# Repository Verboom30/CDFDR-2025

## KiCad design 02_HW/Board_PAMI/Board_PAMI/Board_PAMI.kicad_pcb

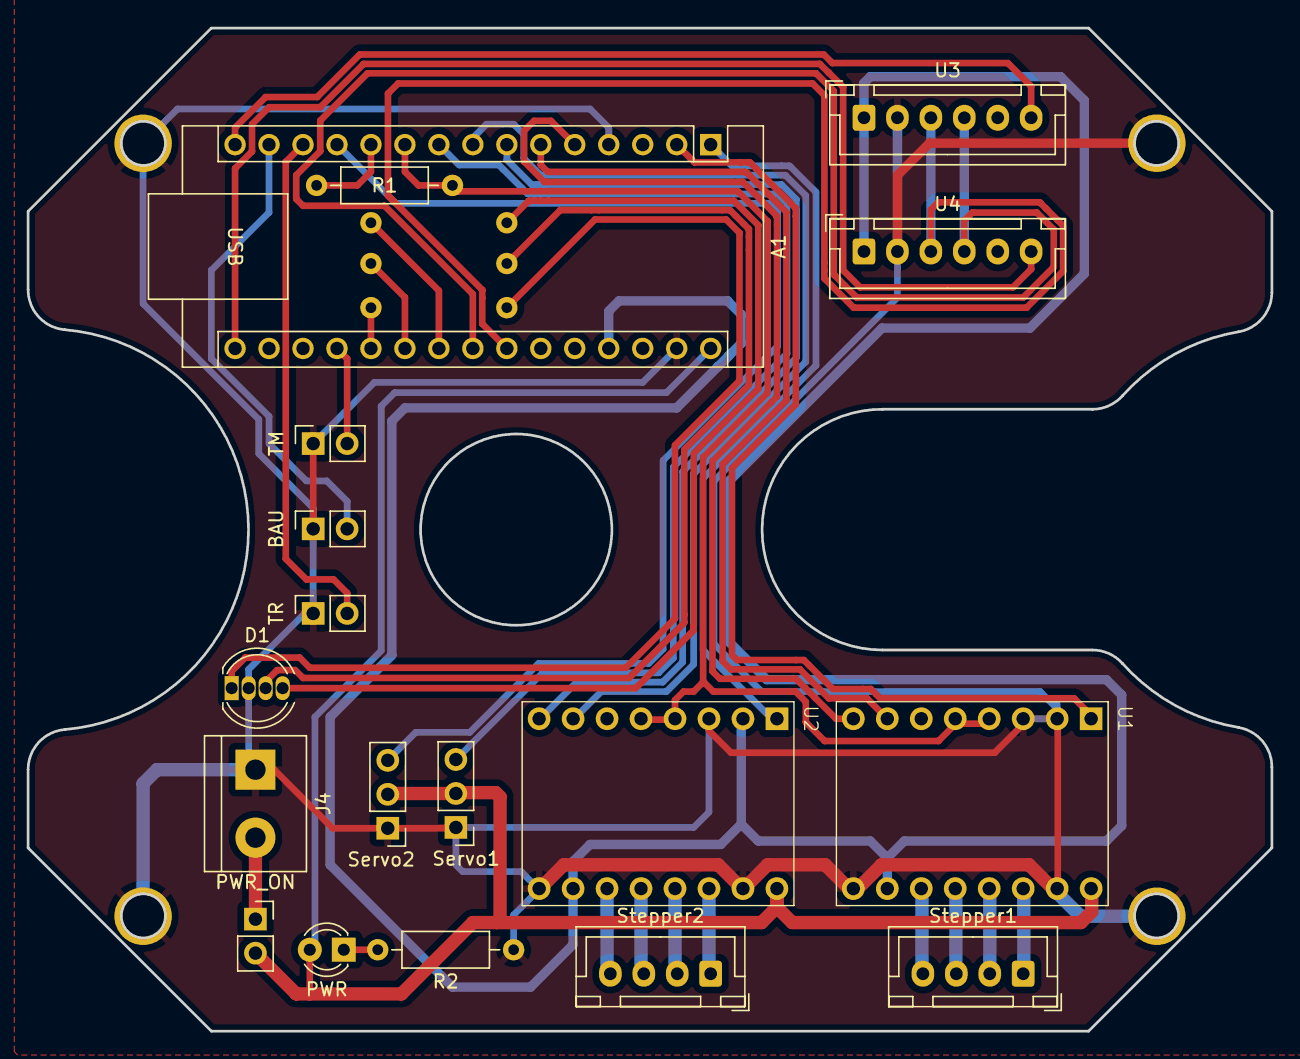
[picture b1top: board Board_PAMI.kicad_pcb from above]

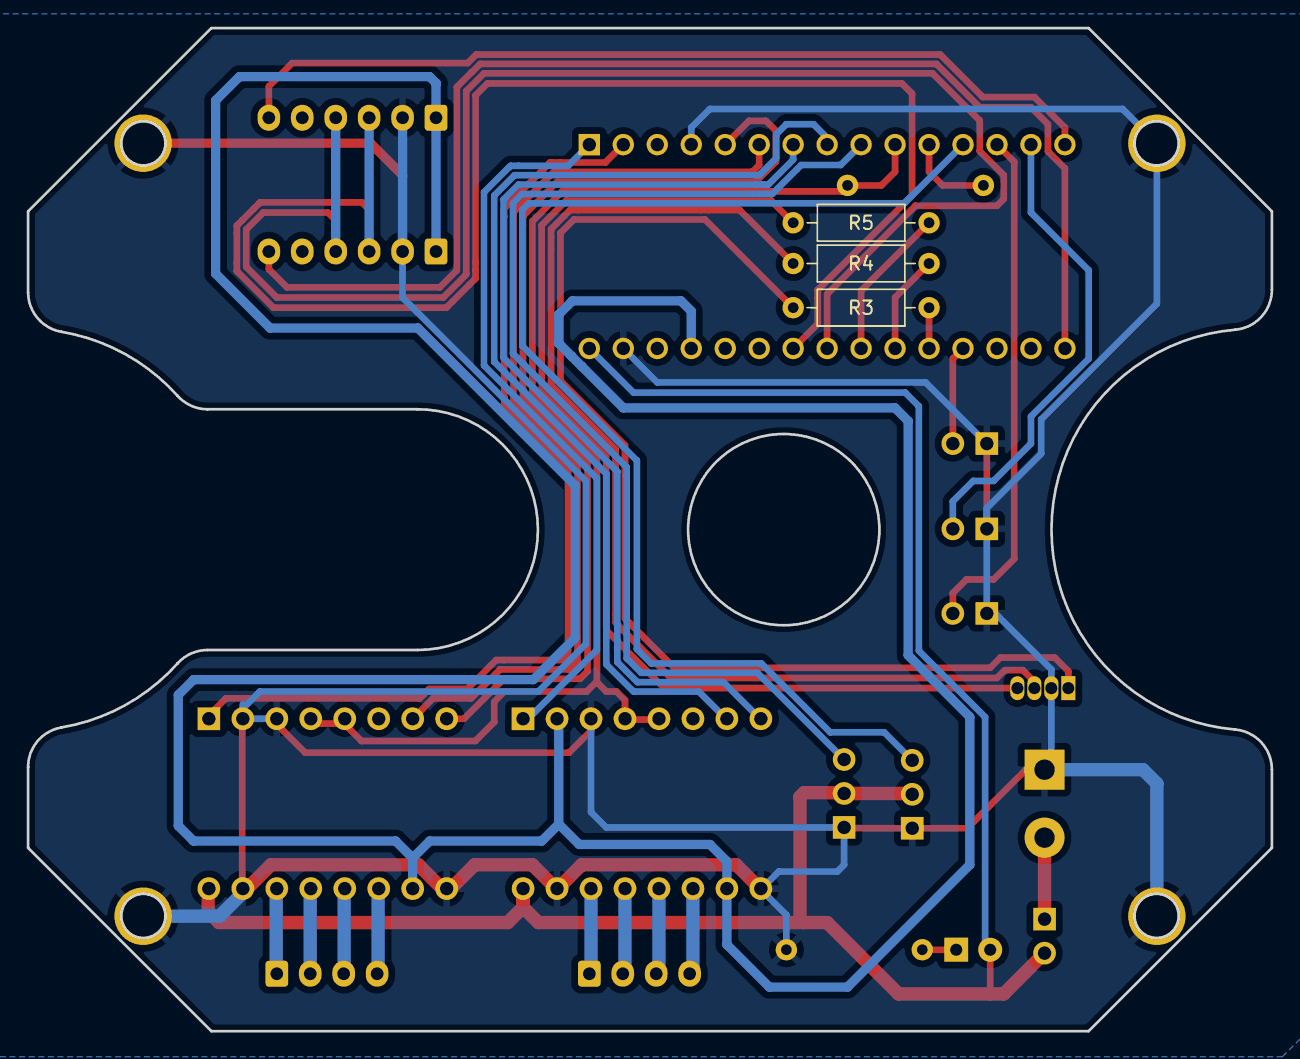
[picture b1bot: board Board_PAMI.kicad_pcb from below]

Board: 2 copper layers, 93.0 x 75.0 mm, 25 parts (3 on the bottom side), 36 nets.

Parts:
A1: Arduino_Nano_v3.x; Arduino_Nano
BAU: SW_BAU; PinSocket_1x02_P2.54mm_Vertical
D1: LED_BGKR; LED_D5.0mm-4_RGB_HOME
H1, H2, H3, H4: MountingHole_Pad; MountingHole_3.2mm_M3_DIN965_Pad_home
J4: ALIM; TerminalBlock_bornier-2_P5.08mm
PWR: LED_PWR; LED_D3.0mm
PWR_ON: PW_ON; PinSocket_1x02_P2.54mm_Vertical
R1: 1K; R_Axial_DIN0207_L6.3mm_D2.5mm_P10.16mm_Horizontal
R2, R3, R4, R5: 220R; R_Axial_DIN0207_L6.3mm_D2.5mm_P10.16mm_Horizontal
Servo1: SERVO_1; PinHeader_1x03_P2.54mm_Vertical
Servo2: SERVO_2; PinHeader_1x03_P2.54mm_Vertical
Stepper1: STEPPER_1; JST_XH_B4B-XH-A_1x04_P2.50mm_Vertical
Stepper2: STEPPER_2; JST_XH_B4B-XH-A_1x04_P2.50mm_Vertical
TM: SW_TEAM; PinSocket_1x02_P2.54mm_Vertical
TR: SW_TIRETTE; PinSocket_1x02_P2.54mm_Vertical
U1, U2: TMC2209
U3, U4: VL53L0XV2; JST_XH_B6B-XH-A_1x06_P2.50mm_Vertical

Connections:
/6V: J4.2, PWR_ON.1 (A)
DIR_1: A1.5 (D2), U1.8 (DIR)
DIR_2: A1.7 (D4), U2.8 (DIR)
EN_STP_1: A1.2 (D0/RX), U1.1 (EN)
EN_STP_2: A1.1 (D1/TX), U2.1 (EN)
GND: A1.4 (GND), A1.29 (GND), BAU.1, D1.3 (K), H1.1, H2.1, H3.1, H4.1, J4.1, R2.1, Servo1.1, Servo2.1, TM.1 (A), TR.1 (A), U1.2 (MS1), U1.3 (MS2), U1.10 (GND), U1.16 (GND), U2.3 (MS2), U2.10 (GND), U2.16 (GND), U3.2 (GND), U4.2 (GND)
LED_B: A1.22 (A3), R5.2
LED_G: A1.21 (A2), R4.2
LED_R: A1.20 (A1), R3.2
unnamed: A1.11 (D8), R1.2
unnamed: D1.1 (BA), R5.1
unnamed: D1.2 (GA), R4.1
unnamed: D1.4 (RA), R3.1
unnamed: PWR.1 (K), R2.2
unnamed: Stepper1.1, U1.11 (A2)
unnamed: Stepper1.2, U1.12 (A1)
unnamed: Stepper1.3, U1.13 (B1)
unnamed: Stepper1.4, U1.14 (B2)
unnamed: Stepper2.1, U2.11 (A2)
unnamed: Stepper2.2, U2.12 (A1)
unnamed: Stepper2.3, U2.13 (B1)
unnamed: Stepper2.4, U2.14 (B2)
PWM_SERVO_1: A1.9 (D6), Servo1.3
PWM_SERVO_2: A1.12 (D9), Servo2.3
SCL: A1.24 (A5), U3.3 (SCL), U4.3 (SCL)
SDA: A1.23 (A4), U3.4 (SDA), U4.4 (SDA)
STEP_1: A1.6 (D3), U1.7 (STEP)
STEP_2: A1.8 (D5), U2.7 (STEP)
SW_BAU: A1.14 (D11), BAU.2
SW_TM: A1.19 (A0), TM.2 (B)
SW_TR: A1.13 (D10), TR.2 (B)
UART_RX: A1.10 (D7), R1.1, U1.4 (UART_RX), U1.5 (UART_TX), U2.4 (UART_RX), U2.5 (UART_TX)
VCC: A1.27 (+5V), U1.15 (VCC), U2.2 (MS1), U2.15 (VCC), U3.1 (VCC), U4.1 (VCC)
VM: A1.30 (VIN), PWR.2 (A), PWR_ON.2 (B), Servo1.2, Servo2.2, U1.9 (VM), U2.9 (VM)
XSHUT_1: A1.15 (D12), U3.6 (XSHUT)
XSHUT_2: A1.16 (D13), U4.6 (XSHUT)

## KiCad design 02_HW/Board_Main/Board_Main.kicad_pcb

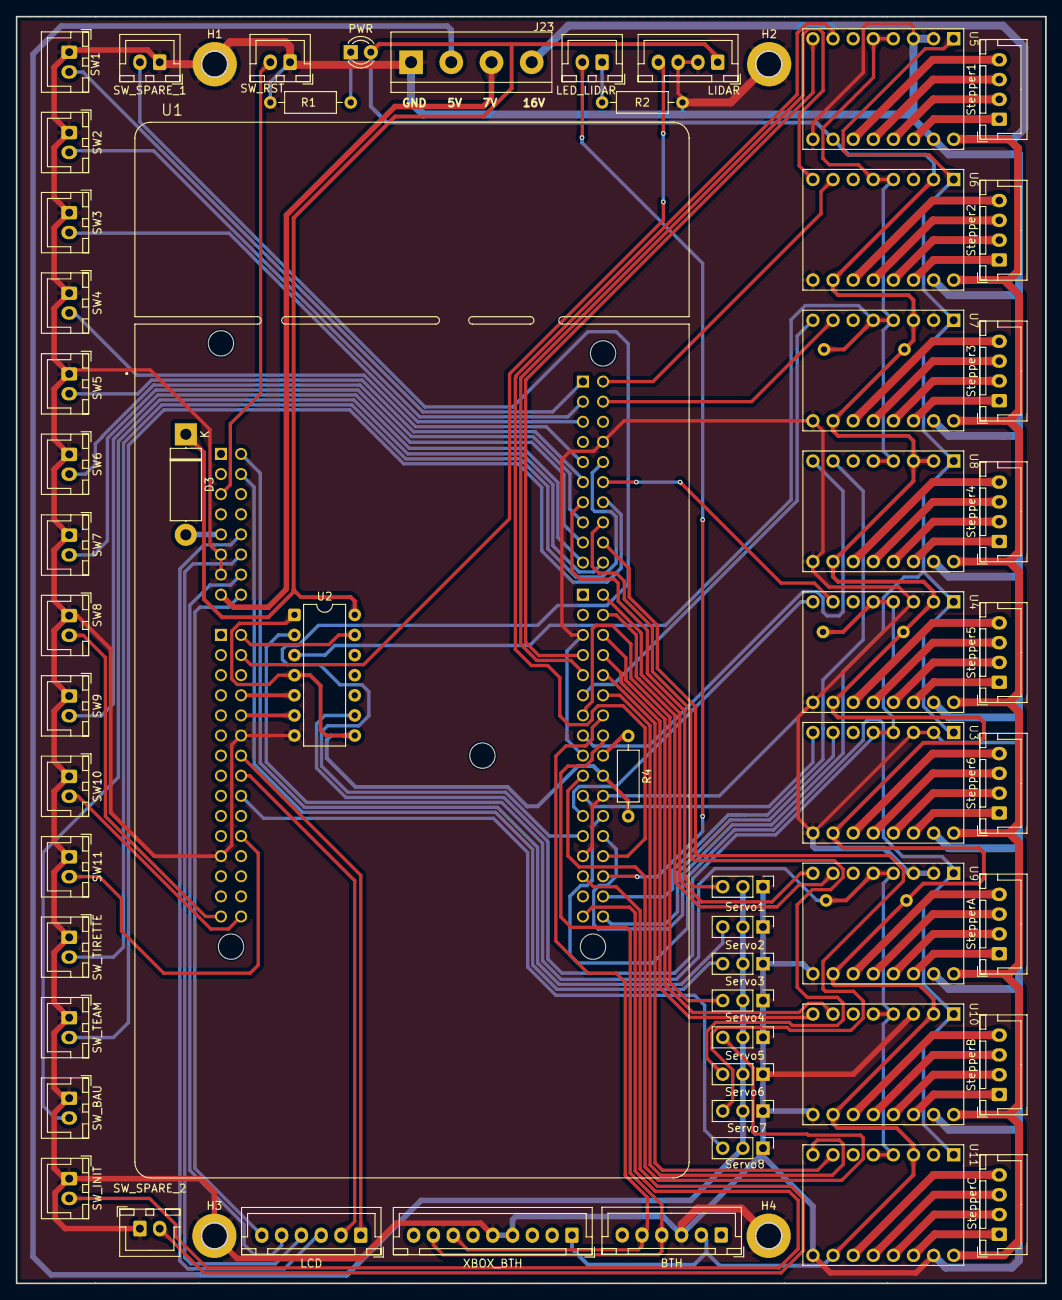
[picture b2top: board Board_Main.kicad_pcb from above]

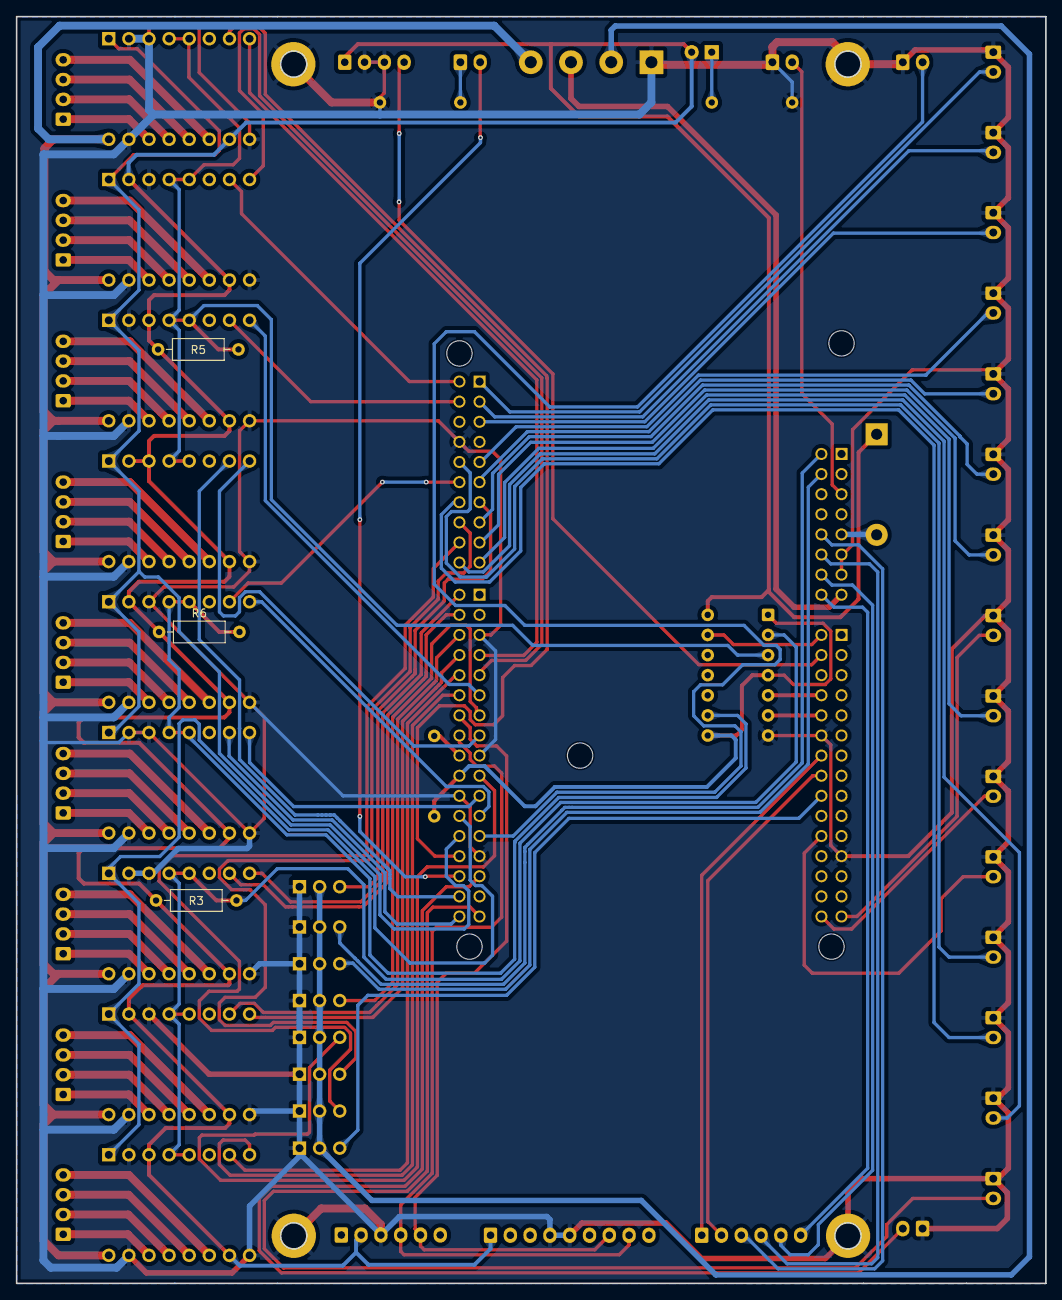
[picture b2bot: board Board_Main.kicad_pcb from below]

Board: 2 copper layers, 130.0 x 160.0 mm, 64 parts (3 on the bottom side), 108 nets.

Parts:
BTH: BTH; JST_XH_B6B-XH-A_1x06_P2.50mm_Vertical
D3: D; D_5W_P12.70mm_Horizontal
H1, H2, H3, H4: MountingHole_Pad; MountingHole_3.2mm_M3_DIN965_Pad
J23: ALIM; TerminalBlock_bornier-4_P5.08mm
LCD: LCD; JST_XH_B6B-XH-A_1x06_P2.50mm_Vertical
LED_LIDAR: LED_LIDAR; JST_XH_B2B-XH-A_1x02_P2.50mm_Vertical
LIDAR: LIDAR; JST_XH_B4B-XH-A_1x04_P2.50mm_Vertical
PWR: LED_PWR; LED_D3.0mm
R1, R2: 220R; R_Axial_DIN0207_L6.3mm_D2.5mm_P10.16mm_Horizontal
R3, R5, R6: 22K; R_Axial_DIN0207_L6.3mm_D2.5mm_P10.16mm_Horizontal
R4: 1K; R_Axial_DIN0207_L6.3mm_D2.5mm_P10.16mm_Horizontal
SW1, SW2, SW3, SW4, SW5, SW6, SW7, SW8, SW9, SW10, SW11: SW_Push; JST_XH_B2B-XH-A_1x02_P2.50mm_Vertical
SW_BAU: SW_BAU; JST_XH_B2B-XH-A_1x02_P2.50mm_Vertical
SW_INIT: SW_INIT; JST_XH_B2B-XH-A_1x02_P2.50mm_Vertical
SW_RST: SW_RST; JST_XH_B2B-XH-A_1x02_P2.50mm_Vertical
SW_SPARE_1: SW_SPARE_1; JST_XH_B2B-XH-A_1x02_P2.50mm_Vertical
SW_SPARE_2: SW_SPARE_2; JST_XH_B2B-XH-A_1x02_P2.50mm_Vertical
SW_TEAM: SW_TEAM; JST_XH_B2B-XH-A_1x02_P2.50mm_Vertical
SW_TIRETTE: SW_TIRETTE; JST_XH_B2B-XH-A_1x02_P2.50mm_Vertical
Servo1: Servo1; PinHeader_1x03_P2.54mm_Vertical
Servo2: Servo2; PinHeader_1x03_P2.54mm_Vertical
Servo3: Servo3; PinHeader_1x03_P2.54mm_Vertical
Servo4: Servo4; PinHeader_1x03_P2.54mm_Vertical
Servo5: Servo5; PinHeader_1x03_P2.54mm_Vertical
Servo6: Servo6; PinHeader_1x03_P2.54mm_Vertical
Servo7: Servo7; PinHeader_1x03_P2.54mm_Vertical
Servo8: Servo8; PinHeader_1x03_P2.54mm_Vertical
Stepper1: Stepper1; JST_XH_B4B-XH-A_1x04_P2.50mm_Vertical
Stepper2: Stepper2; JST_XH_B4B-XH-A_1x04_P2.50mm_Vertical
Stepper3: Stepper3; JST_XH_B4B-XH-A_1x04_P2.50mm_Vertical
Stepper4: Stepper4; JST_XH_B4B-XH-A_1x04_P2.50mm_Vertical
Stepper5: Stepper5; JST_XH_B4B-XH-A_1x04_P2.50mm_Vertical
Stepper6: Stepper6; JST_XH_B4B-XH-A_1x04_P2.50mm_Vertical
StepperA: StepperA; JST_XH_B4B-XH-A_1x04_P2.50mm_Vertical
StepperB: StepperB; JST_XH_B4B-XH-A_1x04_P2.50mm_Vertical
StepperC: StepperC; JST_XH_B4B-XH-A_1x04_P2.50mm_Vertical
U1: NUCLEO-F446ZE; MODULE_NUCLEO-F446ZE
U2: CD4066BE; DIP-14_W7.62mm
U3, U4, U5, U6, U7, U8, U9, U10, U11: TMC2209
XBOX_BTH: XBOX_BTH; JST_XH_B9B-XH-A_1x09_P2.50mm_Vertical

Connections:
BTH_RX: BTH.4, U1.CN10_16 (D0/USART_A_RX/PG_9), XBOX_BTH.8
BTH_TX: BTH.5, U1.CN10_14 (D1/USART_A_TX/PG_14), XBOX_BTH.7
DIR_1: U1.CN10_7 (PB_1), U5.8 (DIR)
DIR_2: U1.CN10_9 (PC_2), U6.8 (DIR)
DIR_3: U1.CN10_11 (PF_4), U7.8 (DIR)
DIR_4: U1.CN10_15 (PB_2), U8.8 (DIR)
DIR_5: U1.CN10_23 (PD_11), U4.8 (DIR)
DIR_6: U1.CN10_21 (PD_12), U3.8 (DIR)
DIR_A: U1.CN10_2 (D7/PF_13), U9.8 (DIR)
DIR_B: U1.CN10_8 (D4/PF_14), U10.8 (DIR)
DIR_C: U1.CN10_12 (D2/PF_15), U11.8 (DIR)
EN_DRIVE_N: U1.CN10_24 (PE_10), U9.1 (EN), U10.1 (EN), U11.1 (EN)
EN_STEP_N: U1.CN10_26 (PE_12), U3.1 (EN), U4.1 (EN), U5.1 (EN), U6.1 (EN), U7.1 (EN), U8.1 (EN)
GND: BTH.3, H1.1, H2.1, H3.1, H4.1, J23.1, LIDAR.2, LIDAR.3, R1.1, R2.1, SW1.1, SW2.1, SW3.1, SW4.1, SW5.1, SW6.1, SW7.1, SW8.1, SW9.1, SW10.1, SW11.1, SW_BAU.1, SW_INIT.1, SW_RST.1, SW_SPARE_1.1, SW_SPARE_2.1, SW_TEAM.1 (A), SW_TIRETTE.1 (A), Servo1.1, Servo2.1, Servo3.1, Servo4.1, Servo5.1, Servo6.1, Servo7.1, Servo8.1, U1.CN7_8 (GND), U1.CN8_11 (GND), U1.CN8_13 (GND), U1.CN9_12 (GND), U1.CN9_23 (GND), U1.CN10_5 (GND), U1.CN10_17 (GND), U1.CN10_22 (GND), U1.CN10_27 (GND), U2.7 (V_{SS}), U3.2 (MS1), U3.3 (MS2), U3.10 (GND), U3.16 (GND), U4.3 (MS2), U4.10 (GND), U4.16 (GND), U5.2 (MS1), U5.3 (MS2), U5.10 (GND), U5.16 (GND), U6.3 (MS2), U6.10 (GND), U6.16 (GND), U7.2 (MS1), U7.10 (GND), U7.16 (GND), U8.10 (GND), U8.16 (GND), U9.2 (MS1), U9.3 (MS2), U9.10 (GND), U9.16 (GND), U10.3 (MS2), U10.10 (GND), U10.16 (GND), U11.2 (MS1), U11.10 (GND), U11.16 (GND), XBOX_BTH.4, XBOX_BTH.5
LCD_D4: LCD.3, U1.CN8_10 (PC_12)
LCD_D5: LCD.4, U1.CN8_12 (PD_2)
LCD_D6: LCD.5, U1.CN8_14 (PG_2)
LCD_D7: LCD.6, U1.CN8_16 (PG_3)
LCD_EN: LCD.2, U1.CN9_16 (PE_4)
LCD_RS: LCD.1, U1.CN9_14 (PE_2)
LED_LIDAR: LED_LIDAR.2 (A), U1.CN10_30 (PE_15)
LIDAR_RX: LIDAR.4, U1.CN9_4 (PD_6)
unnamed: PWR.1 (K), R1.2
unnamed: LED_LIDAR.1 (K), R2.2
unnamed: D3.2 (A), U1.CN8_9 (+5V)
unnamed: Stepper1.1, U5.11 (A2)
unnamed: Stepper1.2, U5.12 (A1)
unnamed: Stepper1.3, U5.13 (B1)
unnamed: Stepper1.4, U5.14 (B2)
unnamed: Stepper2.1, U6.11 (A2)
unnamed: Stepper2.2, U6.12 (A1)
unnamed: Stepper2.3, U6.13 (B1)
unnamed: Stepper2.4, U6.14 (B2)
unnamed: Stepper3.1, U7.11 (A2)
unnamed: Stepper3.2, U7.12 (A1)
unnamed: Stepper3.3, U7.13 (B1)
unnamed: Stepper3.4, U7.14 (B2)
unnamed: Stepper4.1, U8.11 (A2)
unnamed: Stepper4.2, U8.12 (A1)
unnamed: Stepper4.3, U8.13 (B1)
unnamed: Stepper4.4, U8.14 (B2)
unnamed: Stepper5.1, U4.11 (A2)
unnamed: Stepper5.2, U4.12 (A1)
unnamed: Stepper5.3, U4.13 (B1)
unnamed: Stepper5.4, U4.14 (B2)
unnamed: Stepper6.1, U3.11 (A2)
unnamed: Stepper6.2, U3.12 (A1)
unnamed: Stepper6.3, U3.13 (B1)
unnamed: Stepper6.4, U3.14 (B2)
unnamed: StepperA.1, U9.11 (A2)
unnamed: StepperA.2, U9.12 (A1)
unnamed: StepperA.3, U9.13 (B1)
unnamed: StepperA.4, U9.14 (B2)
unnamed: StepperB.1, U10.11 (A2)
unnamed: StepperB.2, U10.12 (A1)
unnamed: StepperB.3, U10.13 (B1)
unnamed: StepperB.4, U10.14 (B2)
unnamed: StepperC.1, U11.11 (A2)
unnamed: StepperC.2, U11.12 (A1)
unnamed: StepperC.3, U11.13 (B1)
unnamed: StepperC.4, U11.14 (B2)
P5V: J23.2, Servo1.2, Servo2.2, Servo3.2, Servo4.2, Servo5.2, Servo6.2, Servo7.2, Servo8.2
P7V: J23.3, U1.CN8_15 (VIN)
PWM_SERVO_1: Servo1.3, U1.CN7_13 (PB_5)
PWM_SERVO_2: Servo2.3, U1.CN8_2 (PC_8)
PWM_SERVO_3: Servo3.3, U1.CN8_4 (PC_9)
PWM_SERVO_4: Servo4.3, U1.CN10_13 (PB_6)
PWM_SERVO_5: Servo5.3, U1.CN10_19 (PD_13)
PWM_SERVO_6: Servo6.3, U1.CN7_16 (D10/PD_14)
PWM_SERVO_7: Servo7.3, U1.CN7_18 (D9/PD_15)
PWM_SERVO_8: Servo8.3, U1.CN9_18 (PE_5)
SEL_UART_0: U1.CN9_2 (PD_7), U2.13
SEL_UART_1: U1.CN9_8 (PD_4), U2.5
SEL_UART_2: U1.CN9_10 (PD_3), U2.6
STEP_1: U1.CN10_28 (PE_14), U5.7 (STEP)
STEP_2: U1.CN7_2 (D15/PB_8), U6.7 (STEP)
STEP_3: U1.CN7_4 (D14/PB_9), U7.7 (STEP)
STEP_4: U1.CN10_32 (PB_10), U8.7 (STEP)
STEP_5: U1.CN7_12 (D12/PA_6), U4.7 (STEP)
STEP_6: U1.CN10_34 (PB_11), U3.7 (STEP)
STEP_A: U1.CN10_4 (D6/PE_9), U9.7 (STEP)
STEP_B: U1.CN10_6 (D5/PE_11), U10.7 (STEP)
STEP_C: U1.CN10_10 (D3/PE_13), U11.7 (STEP)
SW_1: SW1.2, U1.CN7_1 (PC_6)
SW_2: SW2.2, U1.CN7_3 (PB_15)
SW_3: SW3.2, U1.CN7_5 (PB_13)
SW_4: SW4.2, U1.CN7_9 (PA_15)
SW_5: SW5.2, U1.CN7_11 (PC_7)
SW_6: SW6.2, U1.CN7_15 (PB_3)
SW_7: SW7.2, U1.CN7_17 (PA_4)
SW_8: SW8.2, U1.CN9_29 (PG_0)
SW_9: SW9.2, U1.CN7_19 (PB_4)
SW_10: SW10.2, U1.CN9_30 (PG_1)
SW_11: SW11.2, U1.CN9_22 (PE_3)
SW_BAU: SW_BAU.2, U1.CN7_20 (D8/PF_12)
SW_INIT: SW_INIT.2, U1.CN10_33 (PE_0)
SW_RST: SW_RST.2, U1.CN8_5 (NRST)
SW_SPARE_1: SW_SPARE_1.2, U1.CN10_25 (PE_2)
SW_SPARE_2: SW_SPARE_2.2, U1.CN10_29 (PA_0)
SW_TM: SW_TEAM.2 (B), U1.CN7_14 (D11/PA_7)
SW_TR: SW_TIRETTE.2 (B), U1.CN7_10 (D13/FA_5)
UART_AD_0: R3.2, U2.2, U9.4 (UART_RX), U9.5 (UART_TX), U10.4 (UART_RX), U10.5 (UART_TX), U11.4 (UART_RX), U11.5 (UART_TX)
UART_AD_1: R5.2, U2.3, U5.4 (UART_RX), U5.5 (UART_TX), U6.4 (UART_RX), U6.5 (UART_TX), U7.4 (UART_RX), U7.5 (UART_TX), U8.4 (UART_RX), U8.5 (UART_TX)
UART_AD_2: R6.2, U2.9, U3.4 (UART_RX), U3.5 (UART_TX), U4.4 (UART_RX), U4.5 (UART_TX)
UART_RX: R4.2, U1.CN10_20 (PE_7), U2.1, U2.4, U2.8
UART_TX: R4.1, U1.CN10_18 (PE_8)
VBATT_16V: J23.4, U3.9 (VM), U4.9 (VM), U5.9 (VM), U6.9 (VM), U7.9 (VM), U8.9 (VM), U9.9 (VM), U10.9 (VM), U11.9 (VM)
VCC: BTH.2, D3.1 (K), LIDAR.1, PWR.2 (A), R3.1, R5.1, R6.1, U2.14 (V_{DD}), U3.15 (VCC), U4.2 (MS1), U4.15 (VCC), U5.15 (VCC), U6.2 (MS1), U6.15 (VCC), U7.3 (MS2), U7.15 (VCC), U8.2 (MS1), U8.3 (MS2), U8.15 (VCC), U9.15 (VCC), U10.2 (MS1), U10.15 (VCC), U11.3 (MS2), U11.15 (VCC), XBOX_BTH.1

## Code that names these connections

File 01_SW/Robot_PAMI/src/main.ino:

// main.ino
#include <Wire.h>
#include <VL53L0X.h>
#include <AccelStepper.h>
#include <TMCStepper.h>
#include <Thread.h>
#include <ThreadController.h>
#include "Differentiel.h"
#include "UART_TMC.h"
#include "pinout.h"
#include <Servo.h>

 Servo myservo;  // create servo object to control a servo

#define R_SENSE 3.7f


Uart_TMC driverG(TMC_UART_RX, TMC_UART_TX, R_SENSE, 0b00);
Uart_TMC driverD(TMC_UART_RX, TMC_UART_TX, R_SENSE, 0b01);

AccelStepper stepperG(AccelStepper::DRIVER, STEP_G, DIR_G);
AccelStepper stepperD(AccelStepper::DRIVER, STEP_D, DIR_D);
differentiel RobotDiff(&stepperG, &stepperD);

VL53L0X sensor1, sensor2;
ThreadController controller;
Thread ThreadSensors; 
Thread ThreadDrive; 
Thread ThreadShowPos;

int state;
bool StopMove = false;
bool LatchBAU = false;
bool EndMatch = false;
bool CouleurTeam = false; // False team Bleu, True team Jaune
bool StartSequence = false;
bool tiretteRemoved = false;
bool sequenceReady = false;
unsigned long tiretteRemovedTime = 0;

unsigned long servoStartTime = 0;
const long interval = 500; // intervalle en millisecondes
bool ServoState = false;


bool nonBlockingDelay(unsigned long duration, bool reset = false) {
  static unsigned long startTime = 0;
  static bool waiting = false;

  if (reset) {
    startTime = millis();
    waiting = true;
    return false;
  }

  if (waiting && (millis() - startTime >= duration)) {
    waiting = false;
    return true; // Delay terminé
  }

  return false; // Delay encore en cours
}

void checkSensors() {
  int dist1 = sensor1.readRangeContinuousMillimeters();
  int dist2 = sensor2.readRangeContinuousMillimeters();
  StopMove = (dist1 < 150 || dist2 < 150) or LatchBAU or EndMatch;
  digitalWrite(LED_R, (StopMove or LatchBAU) and !EndMatch ); //BAU LED Rouge
  digitalWrite(LED_B, StopMove and !LatchBAU);//Detection obstacle LED Violette
}

void showPosition() {

  //RobotDiff.updatePosition();
  // Serial.print("[Position] X = ");
  // Serial.print(RobotDiff.getPositionX(), 2);
  // Serial.print(" mm | Y = ");
  // Serial.print(RobotDiff.getPositionY(), 2);
  // Serial.print(" mm | Angle = ");
  // Serial.print(RobotDiff.getAlpha(), 2);
  // Serial.println("°");

  Serial.print(RobotDiff.getPositionX(), 2);
  Serial.print(";");
  Serial.print(RobotDiff.getPositionY(), 2);
  Serial.print(";");
  Serial.print(RobotDiff.getAlpha(), 2);
  Serial.print("\r\n");
}
int converalphaTeam(int angle, bool team){
  return (team) ? -angle : angle;
}

void movementPAMI1(){
  bool movementDone = false;
  switch (state) {
    case 0:
      if (sequenceReady){
        RobotDiff.setPosition(2930,1900,-90,CouleurTeam);
        state++;
      }
      break;
    case 1:
      if (sequenceReady){
        movementDone = Robotmoveto(RobotDiff,1175, converalphaTeam(0, CouleurTeam),StopMove);
        if(movementDone) state++;
      }
      break;
    case 2:
        movementDone = Robotmoveto(RobotDiff,0, converalphaTeam(-90, CouleurTeam),StopMove);
        if(movementDone) state++;
      break;

    case 3:
        movementDone = Robotmoveto(RobotDiff,-100, converalphaTeam(0, CouleurTeam),StopMove);
        if(movementDone)  state++;
      break;
    case 4:
      movementDone = Robotmoveto(RobotDiff,380, converalphaTeam(0, CouleurTeam),StopMove);
      if(movementDone) state++;
       
      break;
    case 5:
      movementDone = Robotmoveto(RobotDiff,0, converalphaTeam(-90, CouleurTeam),StopMove);
      if(movementDone) state++;
      break;
    case 6:
    break;
  }
  
}

void movementPAMI2(){
  bool movementDone = false;
  switch (state) {
    case 0:
      if (sequenceReady){
        RobotDiff.setPosition(2930,1775,-90,CouleurTeam);
        delay(1000);
        state++;
      }
      break;
    case 1:
      movementDone = Robotmoveto(RobotDiff,300, converalphaTeam(0, CouleurTeam),StopMove);
      if(movementDone) state++;
      break;
    case 2:
       movementDone = Robotmoveto(RobotDiff,0, converalphaTeam(-45, CouleurTeam),StopMove);
      if(movementDone) state++;
      break;
    case 3:
      movementDone = Robotmoveto(RobotDiff,550, converalphaTeam(0, CouleurTeam),StopMove);
      if(movementDone) state++;
      break;
    case 4:
      movementDone = Robotmoveto(RobotDiff,0, converalphaTeam(45, CouleurTeam),StopMove);
      if(movementDone) state++;
      break;
    case 5:
      movementDone = Robotmoveto(RobotDiff,360, converalphaTeam(0, CouleurTeam),StopMove);
      if(movementDone) state++;
       break;
    break;
  }
}

void movementPAMI3(){
  bool movementDone = false;
  switch (state) {
    case 0:
      if (sequenceReady){
        RobotDiff.setPosition(2930,1625,-90,CouleurTeam);
        state++;
      }
      break;
    case 1:
      movementDone = Robotmoveto(RobotDiff,300, converalphaTeam(0, CouleurTeam),StopMove);
      if(movementDone) state++;
      break;
    case 2:
       movementDone = Robotmoveto(RobotDiff,0, converalphaTeam(-45, CouleurTeam),StopMove);
      if(movementDone) state++;
      break;
    case 3:
      movementDone = Robotmoveto(RobotDiff,250, converalphaTeam(0, CouleurTeam),StopMove);
      if(movementDone) state++;
      break;
    case 4:
      movementDone = Robotmoveto(RobotDiff,0, converalphaTeam(45, CouleurTeam),StopMove);
      if(movementDone) state++;
      break;
    case 5:
      movementDone = Robotmoveto(RobotDiff,1100, converalphaTeam(0, CouleurTeam),StopMove);
      if(movementDone) state++;
       break;
    break;
  }
}

void PAMIAction(){
  unsigned long currentMillis = millis();
  if (currentMillis - servoStartTime >= interval) {
    servoStartTime = currentMillis;  
    if(ServoState == true){
      ServoState = false;
    }else{
      ServoState = true;
    }
    if(!LatchBAU){
      if(ServoState == true){
        myservo.write(7);
      
      }else{
        myservo.write(60);
      }
    }  
  }
}

void taskDrive() {
  
  if(digitalRead(SW_BAU) == LOW and tiretteRemoved) LatchBAU = true;
 
  if (!tiretteRemoved) {
    if (digitalRead(SW_TEAM) == HIGH) {
        CouleurTeam = true;
        digitalWrite(LED_R, HIGH);
        digitalWrite(LED_G, HIGH);
        digitalWrite(LED_B, LOW);
    }else{
        CouleurTeam = false;
        digitalWrite(LED_R, LOW);
        digitalWrite(LED_G, LOW);
        digitalWrite(LED_B, HIGH);
    }
    myservo.write(60);
  }

  if (!tiretteRemoved && digitalRead(TIRETTE) == HIGH) {
    tiretteRemoved = true;
    tiretteRemovedTime = millis();
  }
  if (tiretteRemoved && !sequenceReady && (millis() - tiretteRemovedTime >= DELAY_START)) {
    sequenceReady = true;
    digitalWrite(LED_R, LOW);
    digitalWrite(LED_G, LOW);
    digitalWrite(LED_B, LOW);
  }

  if (tiretteRemoved && sequenceReady && (millis() - tiretteRemovedTime >= DELAY_END)) {
    EndMatch = true;
    PAMIAction();
  }

#ifdef PAMI_1
  movementPAMI1();
#endif

#ifdef PAMI_2
  movementPAMI2();
#endif

#ifdef PAMI_3
  movementPAMI3();
#endif

  
}

void setupSensors() {
  pinMode(XSHUT_1, OUTPUT);
  pinMode(XSHUT_2, OUTPUT);
  digitalWrite(XSHUT_1, HIGH);
  digitalWrite(XSHUT_2, LOW);

  Wire.begin();
  sensor1.setTimeout(500);
  sensor1.init();
  sensor1.setAddress(1);

  digitalWrite(XSHUT_2, HIGH);
  sensor2.setTimeout(500);
  sensor2.init();
  sensor2.setAddress(2);

  sensor1.startContinuous();
  sensor2.startContinuous();
}

void setup() {
  #ifdef DEBUG
  Serial.begin(230400);
  #endif
  pinMode(LED_R, OUTPUT);
  pinMode(LED_G, OUTPUT);
  pinMode(LED_B, OUTPUT);
  pinMode(SW_BAU, INPUT_PULLUP);
  pinMode(TIRETTE, INPUT_PULLUP);
  pinMode(SW_TEAM, INPUT_PULLUP);

  digitalWrite(LED_R, LOW);
  digitalWrite(LED_G, LOW);
  digitalWrite(LED_B, LOW);

  setupSensors();

  driverG.setup_stepper();
  driverD.setup_stepper();
  delay(500);
  myservo.attach(SERVO_1);  // attaches the servo on pin 9 to the servo object

  ThreadSensors.onRun(checkSensors);
  ThreadSensors.setInterval(300);

  ThreadDrive.onRun(taskDrive);
  ThreadDrive.setInterval(1);
  #ifdef DEBUG
  ThreadShowPos.onRun(showPosition);
  ThreadShowPos.setInterval(1);
  #endif

  controller.add(&ThreadSensors);
  controller.add(&ThreadDrive);
  #ifdef DEBUG
  controller.add(&ThreadShowPos);
  #endif

}

void loop() {
  controller.run();
}

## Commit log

2025-01-24 Mise sous forme de class
2025-01-24 Ajout des registres UART
2025-01-25 Ajout des registres de conf
2025-01-25 move stepper
2025-01-25 Ajout de la class holonome
2025-01-26 Ajout de la class SerialTMC
2025-01-26 Uart 3 steppers
2025-01-26 holonome.cpp
2025-01-27 test 3 steppers OK
2025-03-15 init PAMI
2025-03-15 PAMI test stepper OK
2025-04-05 test stepper TMC
2025-04-05 Kicad
2025-04-09 Update pinout
2025-04-09 test servo
2025-04-11 Fix LCD, LCD on board not PCB
2025-04-11 Uart_TMC
2025-04-11 folder update
2025-04-12 Test StepperC
2025-04-12 Deplacement OK
2025-04-13 LinearActuator
2025-04-13 debug Stepper
2025-04-14 test Stepper ok
2025-04-14 LinearActuator Done OK
2025-04-14 LinearActuator Init OK
2025-04-14 gitignore
2025-04-14 gitignore HW
2025-04-14 Revert "LinearActuator Init OK"
    This reverts commit d65db0a73475f8fb81b528ccc01d3694f585581c.
2025-04-15 LinearActuator Up and Down
2025-05-03 PAMI Pinout
2025-05-03 PAMI Stepper Gauche OK
2025-05-03 Stepper G et D OK
2025-05-03 PAMI avance
2025-05-06 PAMI lecture VL530X
2025-05-06 PAMI MovetoPoint
2025-05-06 PAMI Start and Stop
2025-05-08 Setup Actuator
2025-05-10 construction gradin
2025-05-11 drop Banner
2025-05-12 Move same time LinearActuator
2025-05-12 Main module for the platform
2025-05-12 test move
2025-05-12 Control of the Exterior Pince Rotation
2025-05-12 Trailing whitespace cleaning
2025-05-13 Differentiel Update with mutex and Semaphore
2025-05-13 Config Speed Done
2025-05-13 Deplacement relatif sur la table
2025-05-13 Deplacement absolu sur la table
2025-05-14 inversion Alpha
2025-05-14 Add Proccesing
2025-05-14 déplacement OK
2025-05-14 Correction erreur déplacement X Y
2025-05-14 Config Alpha
2025-05-14 Test strategie
2025-05-15 Correction dérive déplacement Soft
2025-05-15 Test strategie construction_gradin_niveau_2 first done
2025-05-15 correction Alpha
2025-05-16 construction_gradin_niveau_2, setPosition
2025-05-18 test 360 avec roue 15mm Done
2025-05-18 Step up 90 Radius
2025-05-19 construction 2 gradins
2025-05-19 strategie 2 gradins Done
2025-05-19 differentiel
2025-05-20 PAMI move relatif
2025-05-20 Setup PAMI Done
2025-05-21 PAMI move absolu
2025-05-21 PAMI move run and stop
2025-05-22 PAMI Superstar Jaune
2025-05-23 strategie 3 gradins Done + Temp de match et score
2025-05-25 Setup lidar
2025-05-25 Print Lidar
2025-05-25 Traitement trame Lidar Done
2025-05-25 LidarAnalyzer
2025-05-26 Test Lidar Start and Stop
2025-05-26 Robot Start and Stop with SW_init
2025-05-27 Test Config Lidar OK
2025-05-27 Lidar Config aux petit oignons
2025-05-27 Arret D'urgence !
2025-05-27 Changement d'équipe
2025-05-27 Score !
2025-05-28 PAMI BAU + couleur Team
2025-05-28 Delay non bloquant done PAMI
2025-05-28 Kameleon Config Lidar
2025-05-29 Pas toucher Kameleon !!!
2025-05-29 Sequence PAMI 1 2 3 Done
2025-05-30 Test Haute vitesse Kameleon
2025-05-30 Kameleon vitesse slow2
2025-05-30 PAMI serie 4
2025-05-30 test 3 gradins
2025-05-31 construction_gradin_niveau_3 !!!
2025-05-31 Serie 5
2025-06-01 3 gradins match final
